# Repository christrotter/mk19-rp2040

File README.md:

# mk19-rp2040
Attempting to reduce soldering to a minimum - only need to solder the JST-XH headers.  This is the mainboard for the [ArcBoard-mk19](https://github.com/christrotter/qmk_firmware/tree/arcboard-series/keyboards/handwired/arcboard_mk19).

# Features
- On-board RP2040 w. 16MB flash (_based on splinktegrated and reference design_)
- USB-C connectivity for main, split, and screen indicators
- Boot and reset button headers
- Serial vbus power protection (_ESD, polyfuse, diode, etc_)
- External 5v input for LED power (_polyfuse, diode_)
- SPI shift registers to handle rows and cols - up to 256 keys per half - with row/col pin breakouts
- SPI LCD outputs via 0.5mm FPC connectors
- 0.3mm FPC connector for [Cyboard](https://www.cyboard.digital/product-page/dactyl-flex-pcbs) connectivity (or via [this](https://github.com/christrotter/mk19-flex-pcb))
- 0.5mm [macropad](https://github.com/christrotter/macropad-pcb) connector
- Dpad input with diodes (_[RKJXT w. encoder](https://github.com/christrotter/rkjxt-mini-breakout), [5-way](https://github.com/christrotter/5way-pcb), or [4-switch dpad](https://github.com/christrotter/microswitch-dpad)_)
- PMW33XX connector
- 2x [Ultrafalcon](https://github.com/christrotter/ultrafalcon) connectors
- VaniLED connector (_GND,5V,4 gpio; for controlling a secondary RP2040 that handles extra LEDs_)
- Audio, debug, spare pin, power breakouts
- Split-handedness pin solder jumper
- Optional SPI clock pull-down and SPI MISO pull-up resistors
- Test points

# Functional notes
- The LED DI/DO chain flows from main keys (_Cyboard_) to the macropad, then to the dpad (_bodged in post-production_), then UF1, UF2, keybar, screen indicators.
- ROW2COL
- Power LED only indicates you have 5v to the board
- Requires QMK's 'matrix lite' custom matrix feature
  - For more info regarding the custom matrix and shift register implementation, see here: https://github.com/christrotter/shift-register-spi-breakout-pcb
- With everything running it sits at around 1500 scan rate
- First flashing requires holding boot while plugging in main USB; subsequent flashes can use double-press reset button or `QK_BOOT`

# Production notes
- Due to putting the v-cuts on the edge cuts layer, all pcb renders are broken.  This is a known bug in JLC's process.  The pre-production verifications render correctly.
- Requires standard assembly which is a big price increase.
- Make sure to have 'production file verification' checked for PCB and PCBA.

## Post-production fixes
- USB lines were backwards
- Two pins (2 & 5) on the flash were reversed
- The v-cuts were on the wrong layer (should be on the edge cuts layer for JLC)

# PCB overview

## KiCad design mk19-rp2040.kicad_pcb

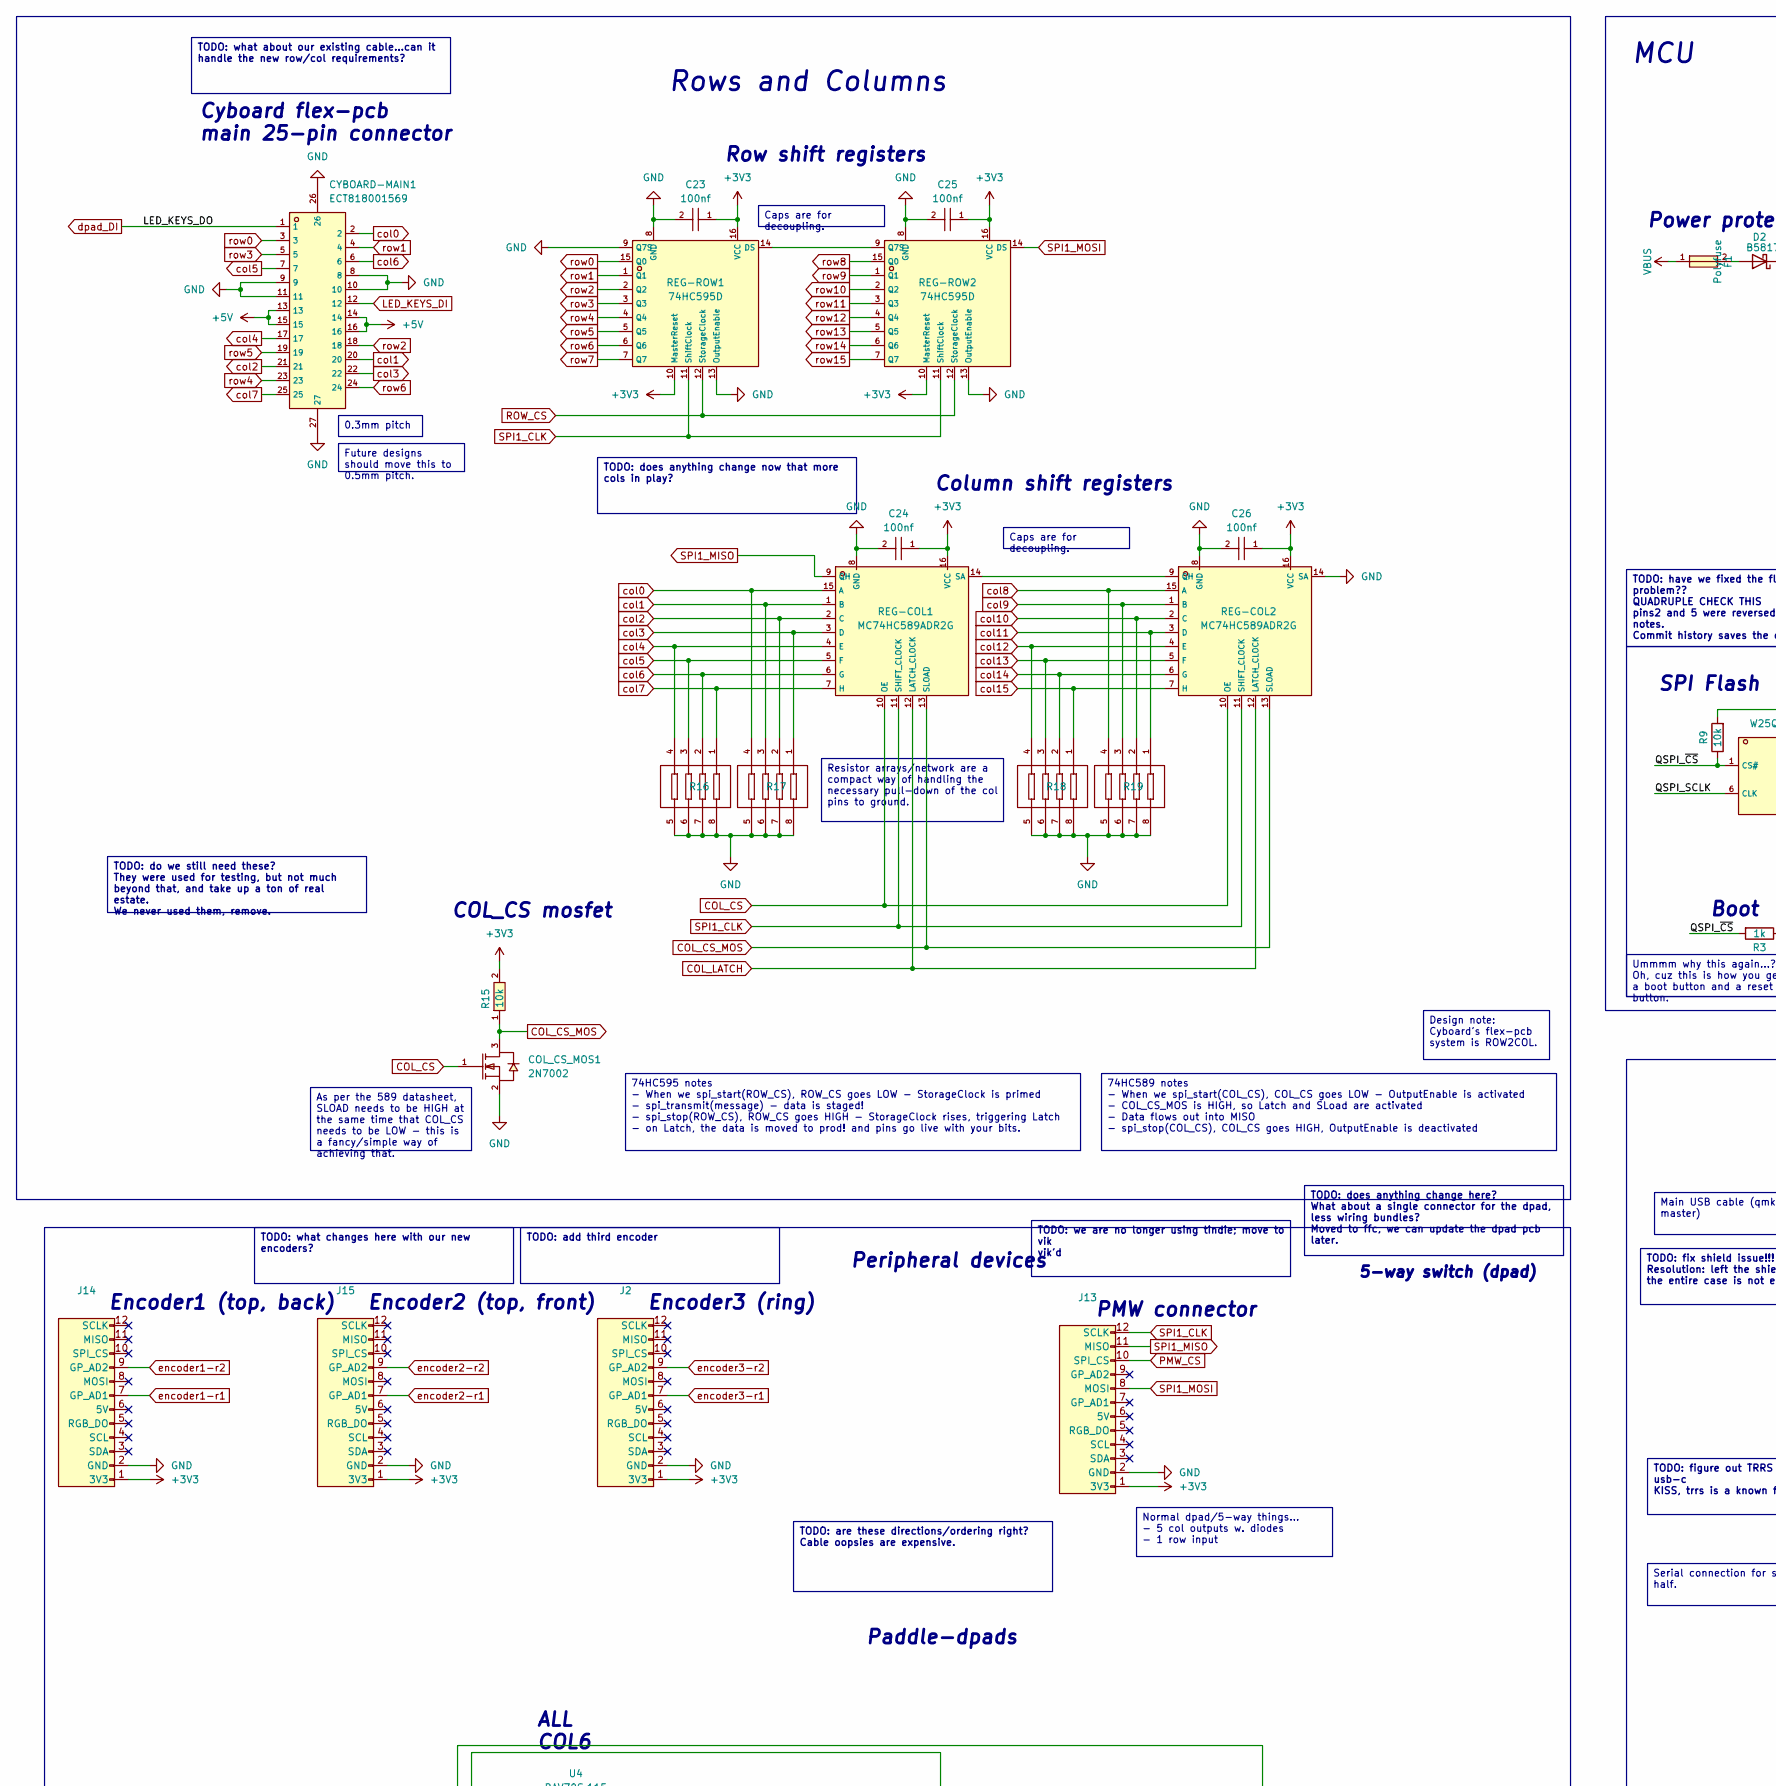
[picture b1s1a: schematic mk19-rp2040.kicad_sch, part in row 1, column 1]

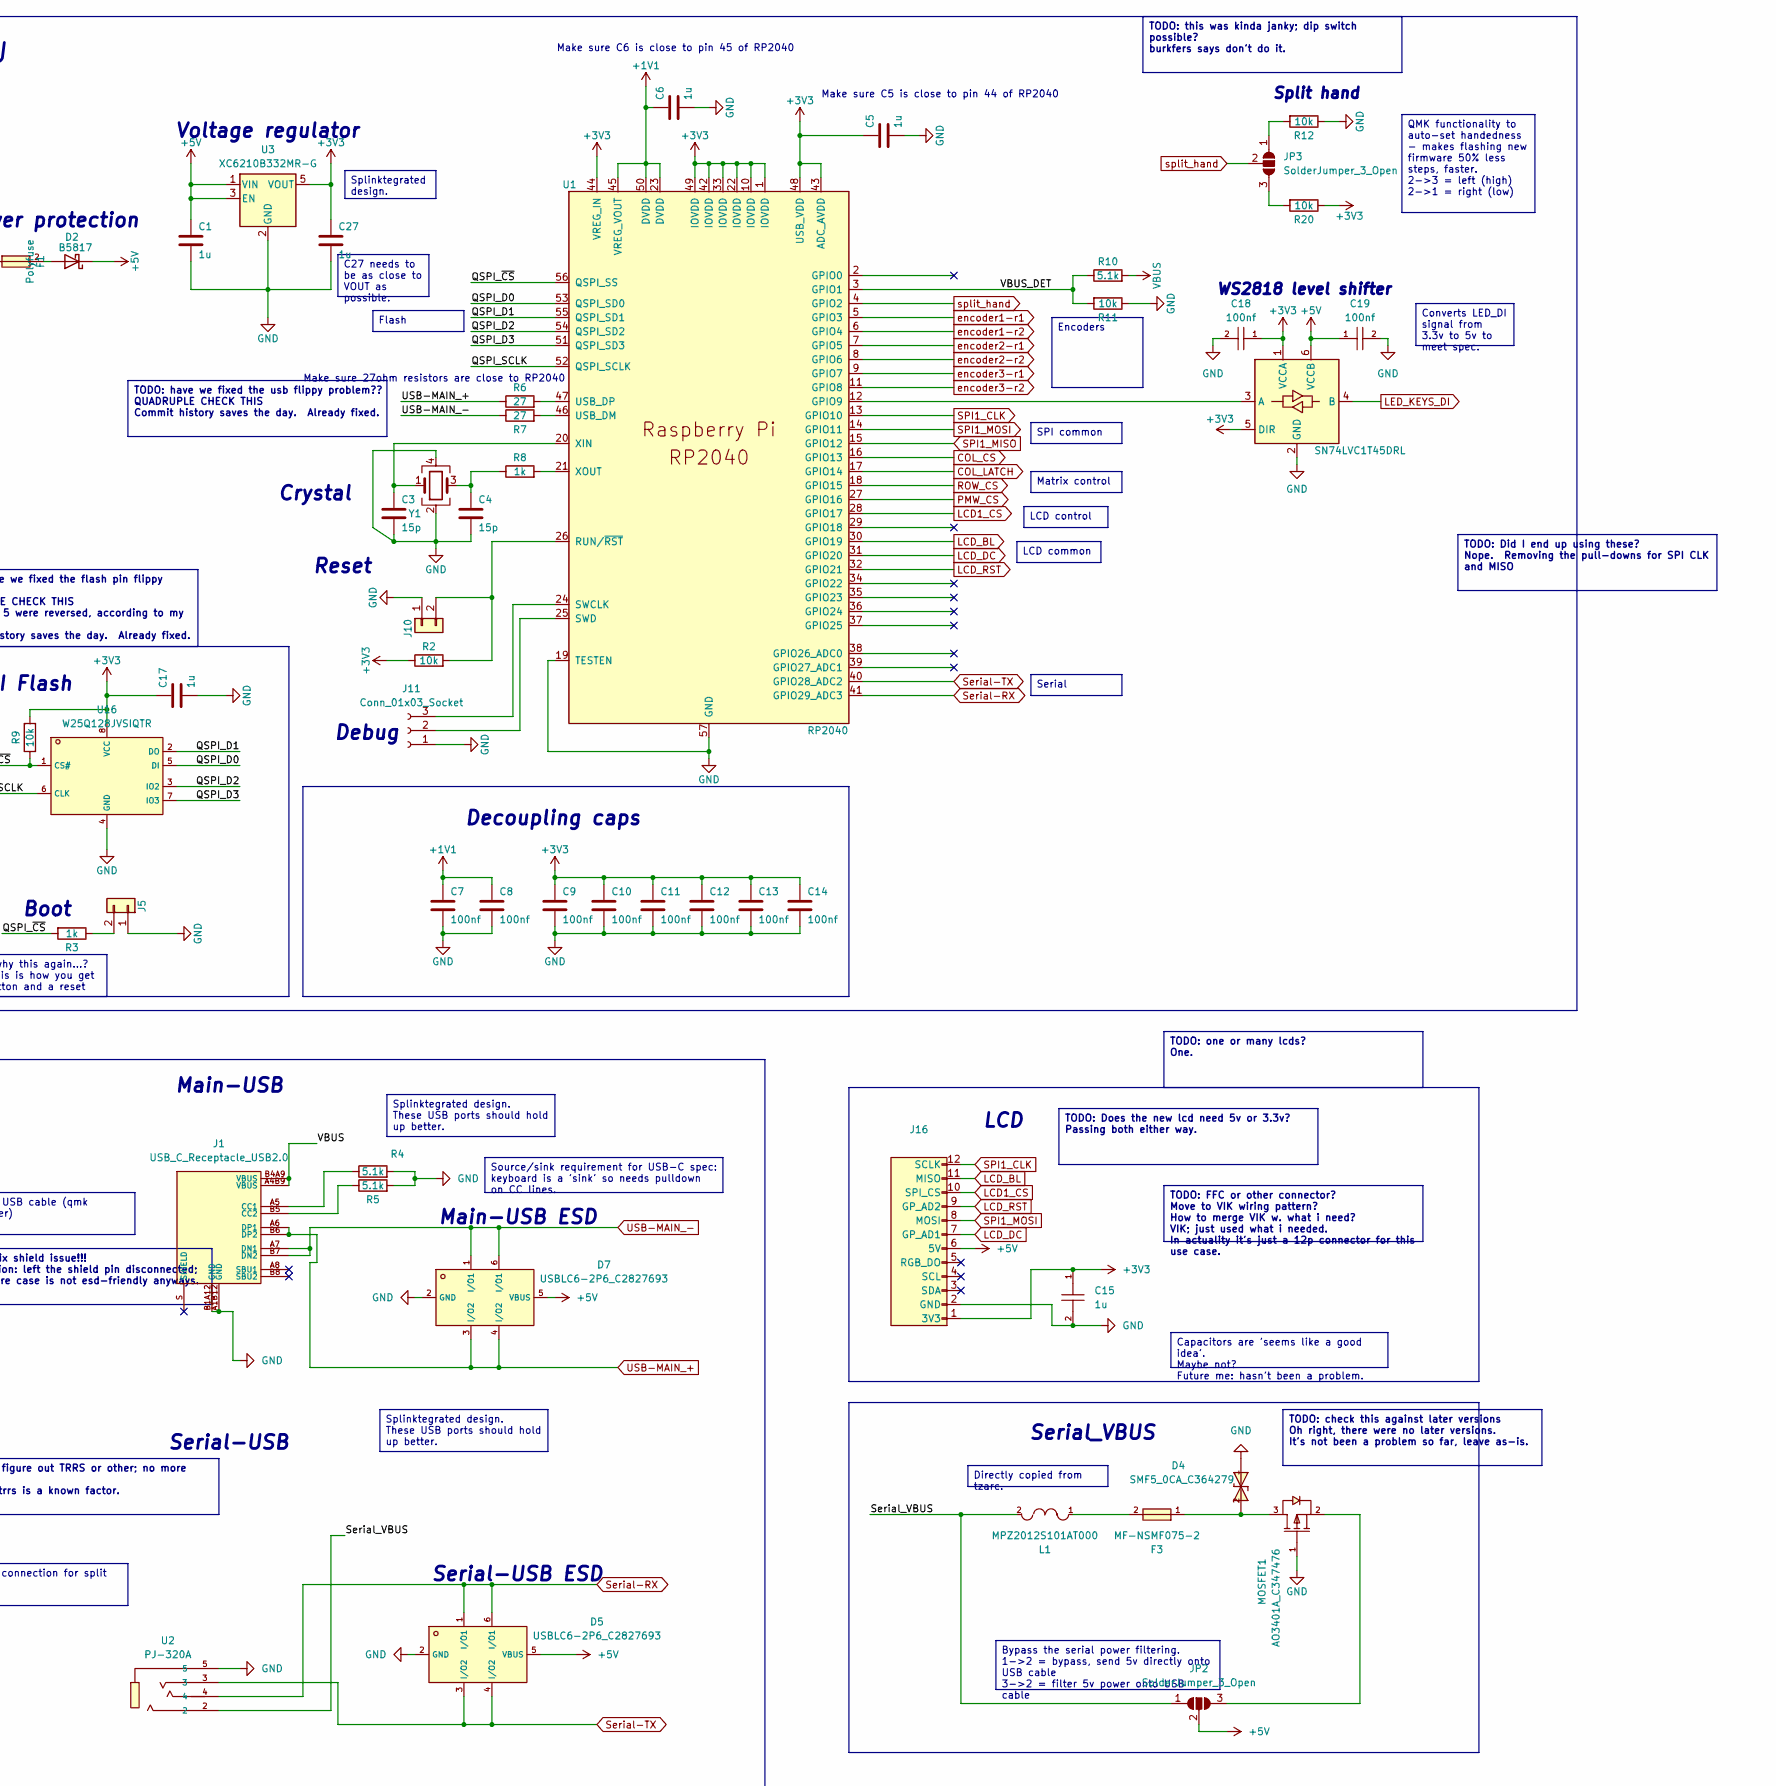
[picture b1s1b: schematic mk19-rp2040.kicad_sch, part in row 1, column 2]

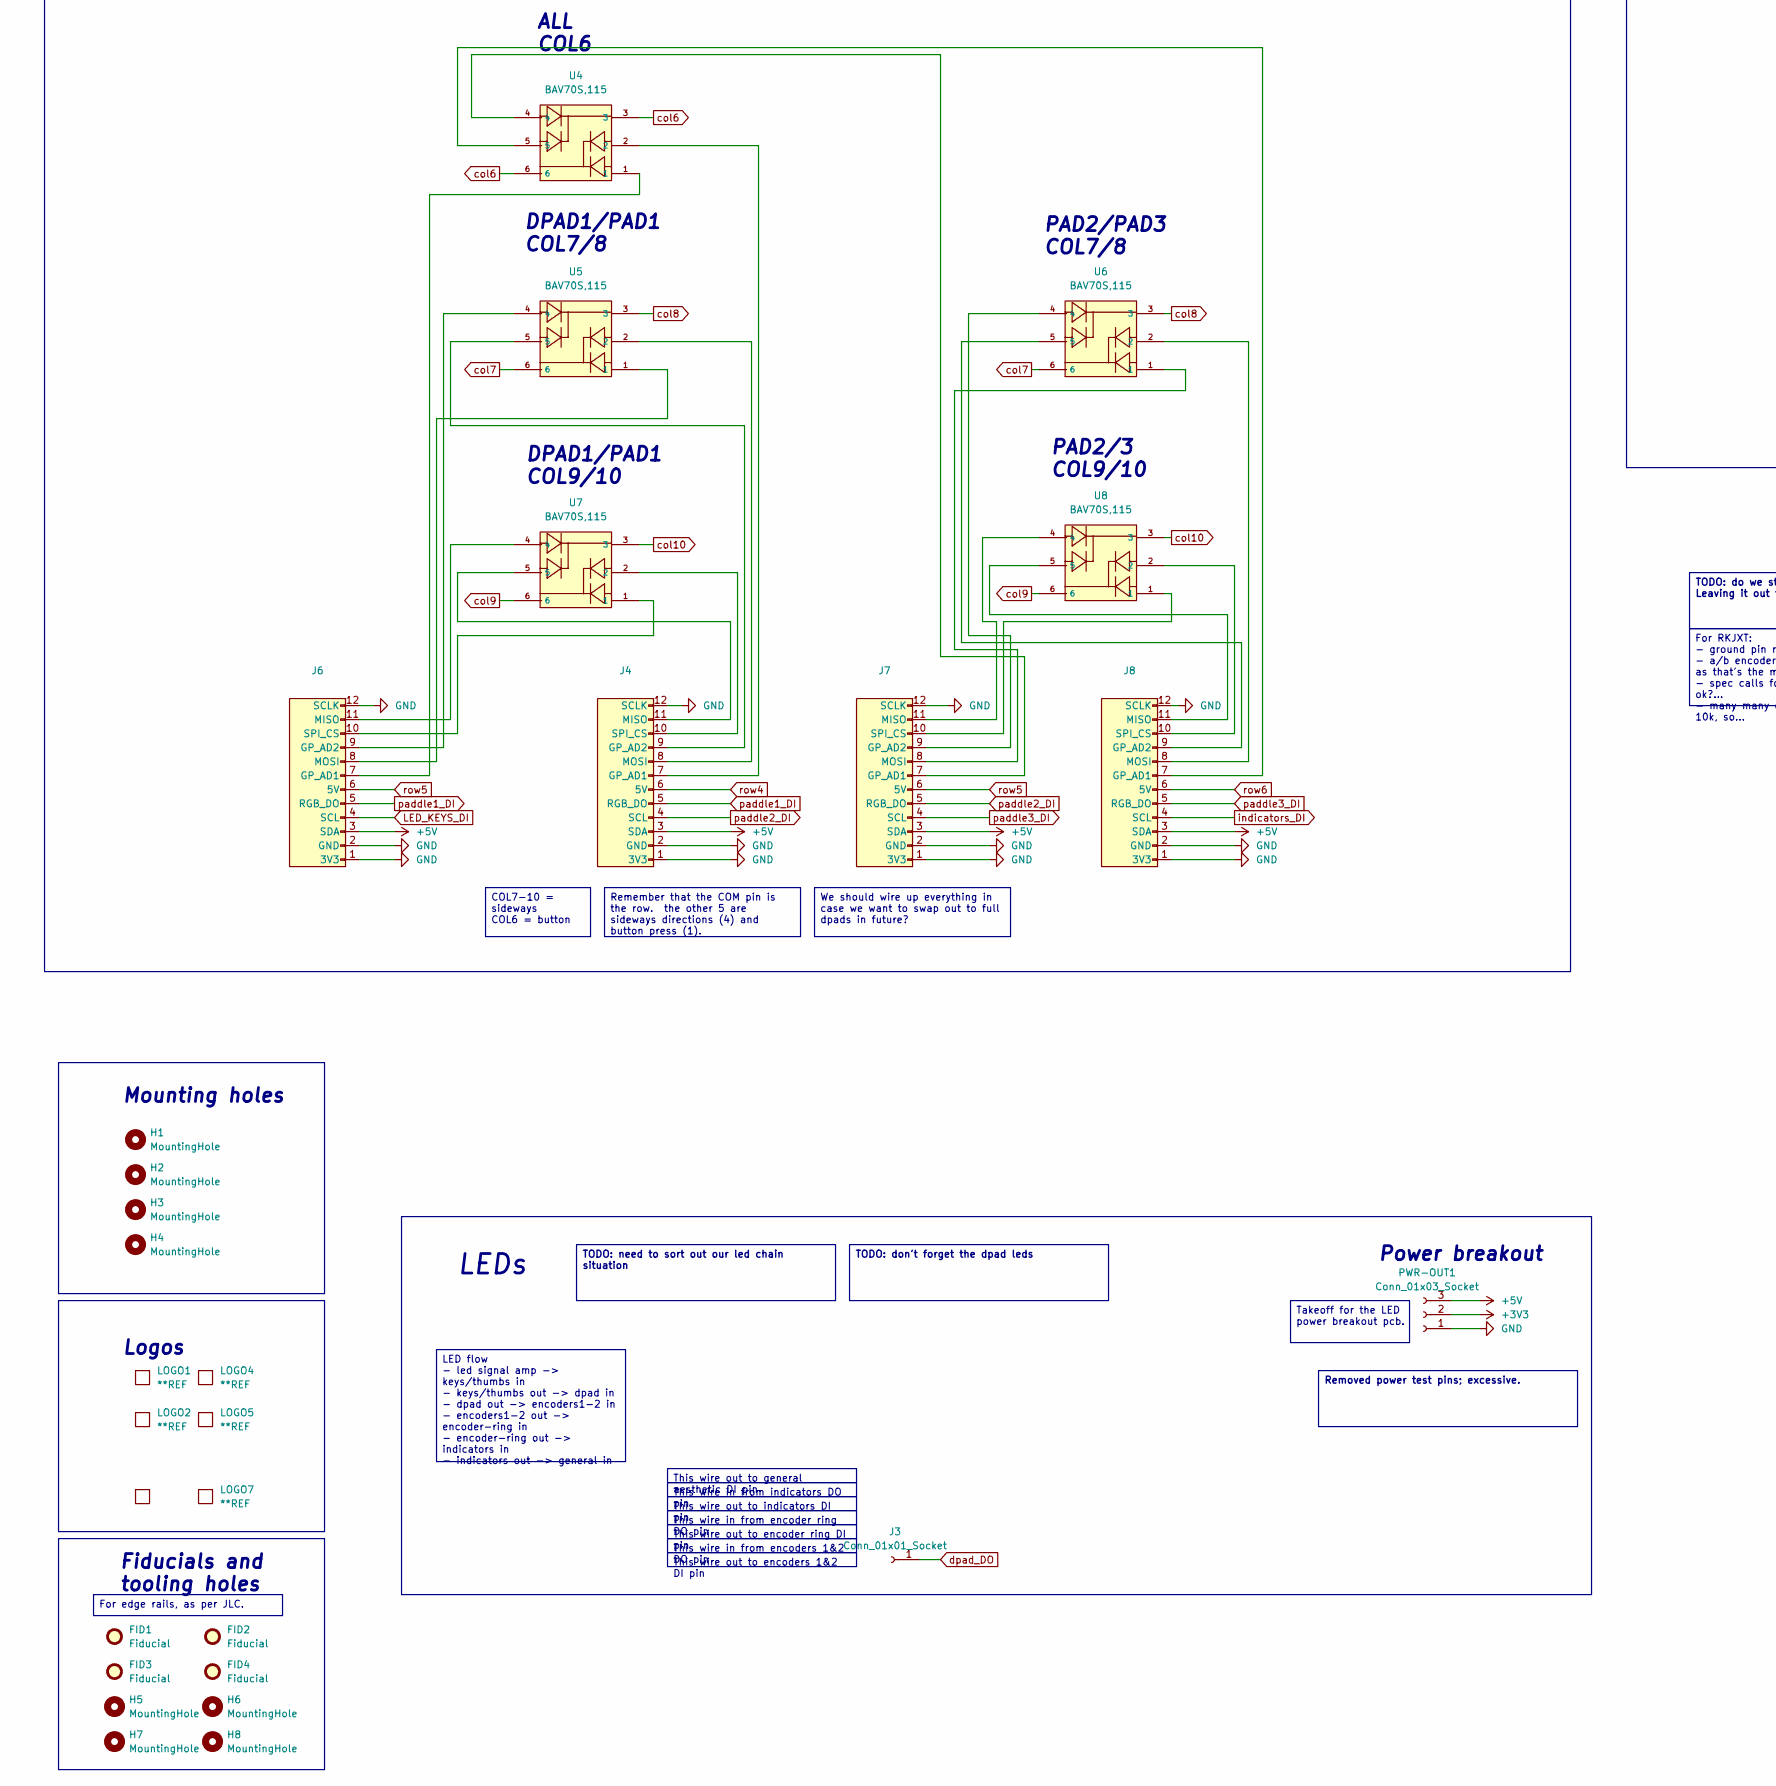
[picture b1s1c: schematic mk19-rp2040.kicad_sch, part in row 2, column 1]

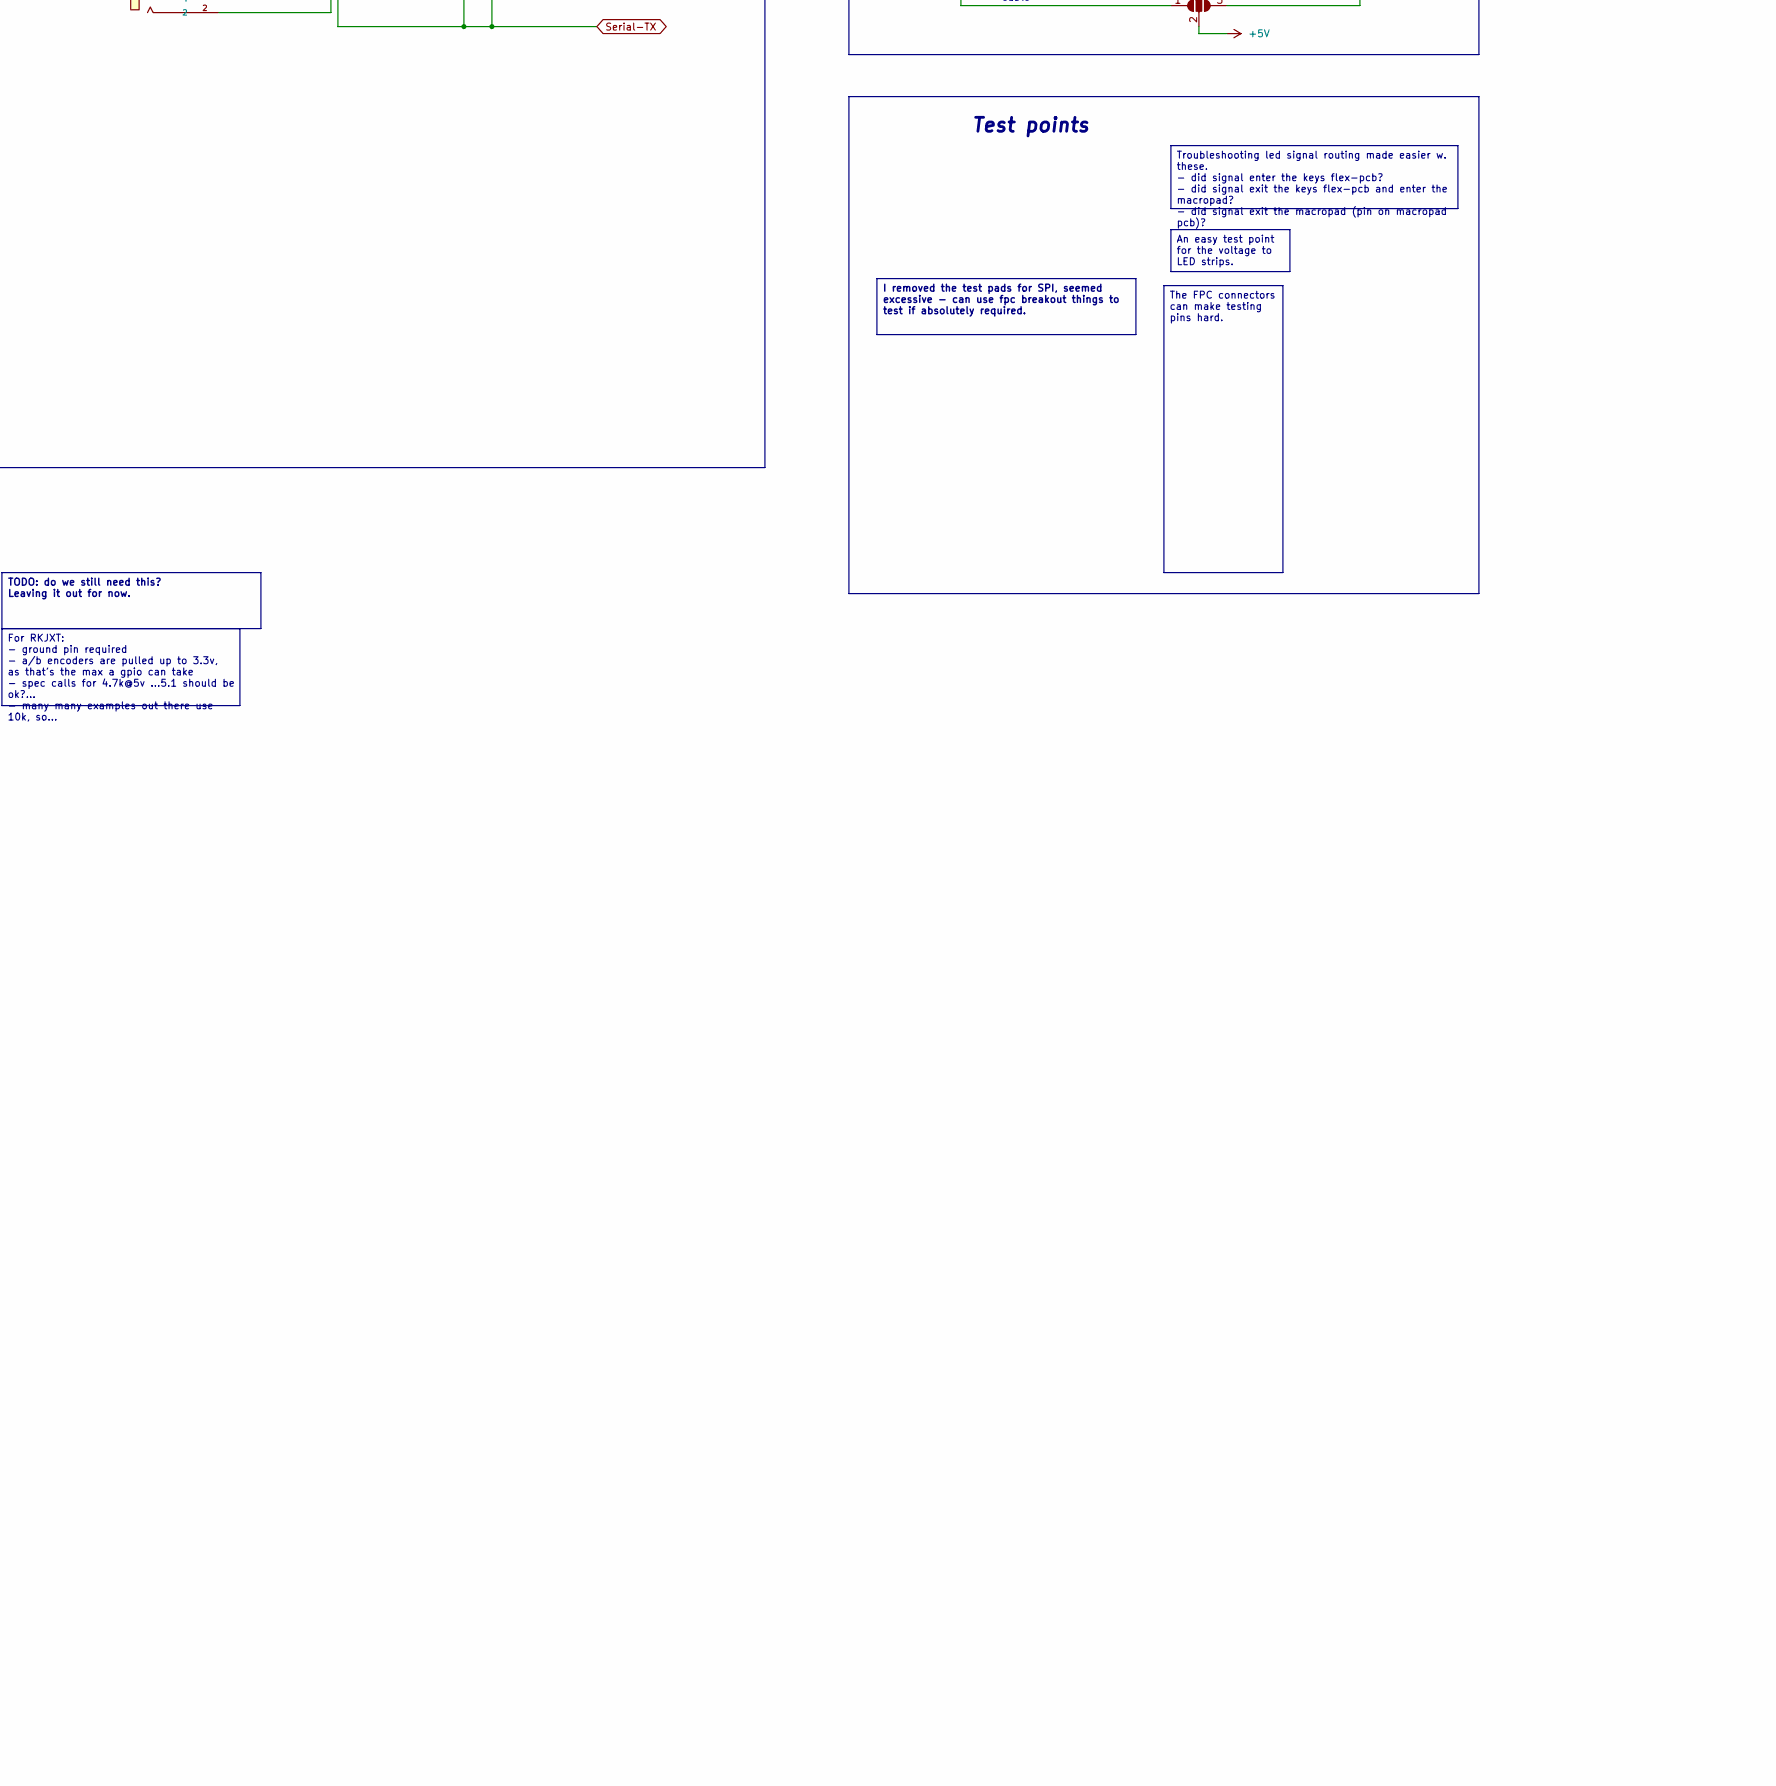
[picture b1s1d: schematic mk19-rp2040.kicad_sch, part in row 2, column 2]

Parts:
C1, C5, C6, C15, C17, C27: 1u; C0402; LCSC C52923
C3, C4: 15p; C0402; LCSC C1548
C7, C8, C9, C10, C11, C12, C13, C14, C18, C19, C23, C24, C25, C26: 100nf; C0402; LCSC C1525
COL_CS_MOS1: 2N7002; SOT-23-3_L2.9-W1.3-P1.90-LS2.4-BR; LCSC C8545
CYBOARD-MAIN1: ECT818001569; FPC-SMD_ECT818001569; LCSC C711420
D2: B5817; D_SOD-323; LCSC C123899
D4: SMF5_0CA_C364279; SOD-123FL_L2.8-W1.8-LS3.7-BI; LCSC C364279
D5, D7: USBLC6-2P6_C2827693; SOT-666-6_L1.6-W1.2-P0.50-LS1.6-BL; LCSC C2827693
F1: Polyfuse; F1206; LCSC C2892425
F3: MF-NSMF075-2; F1206; LCSC C89653
FID1, FID2, FID3, FID4: Fiducial; Fiducial_1mm_Mask3mm
H1, H2, H3, H4: MountingHole; MountingHole_3.2mm_M3_Pad_Via
H5, H6, H7, H8: MountingHole; hole-tooling-2mm
J1: USB_C_Receptacle_USB2.0; USB-C-SMD_12P-P0.50-H-F_TYPE-C-31-M-14; LCSC C223907
J2, J4, J6, J7, J8, J13, J14, J15, J16: FFC-SMD_FFC05001-12SBA124W5M
J3: Conn_01x01_Socket; PinHeader_1x01_P2.54mm_Vertical
J5, J10: Conn_01x02; PinSocket_1x02_P2.54mm_Vertical
J11: Conn_01x03_Socket; PinHeader_1x03_P2.54mm_Vertical
JP2, JP3: SolderJumper_3_Open; SolderJumper-3_P1.3mm_Open_Pad1.0x1.5mm
L1: MPZ2012S101AT000; L0805; LCSC C15957
LED-LVL1: SN74LVC1T45DRL; SOT-563_L1.6-W1.2-P0.50-LS1.6-BR; MPN SN74LVC1T45DRLR; JLC Basic N
LOGO1, LOGO4: **REF; awesome-logo
LOGO2, LOGO5: **REF; qmk-lite
LOGO7: **REF; cyboard-logo-10mm
LOGO8: **REF; qr-mk19-rp2040-10mm
MOSFET1: AO3401A_C347476; SOT-23_L2.9-W1.3-P1.90-LS2.4-BR; LCSC C15127
PWR-OUT1: Conn_01x03_Socket; PinHeader_1x03_P2.54mm_Vertical
R2, R9, R11, R12, R15, R20: 10k; R0402; LCSC C25744
R3, R8: 1k; R0402; LCSC C11702
R4, R5, R10: 5.1k; R0402; LCSC C25905
R6, R7: 27; R0402; LCSC C25100
R16, R17, R18, R19: 4D03WGJ0103T5E; RES-ARRAY-SMD_0603-8P-L3.2-W1.6-BL; LCSC C29718
REG-COL1, REG-COL2: MC74HC589ADR2G; SOIC-16_L9.9-W3.9-P1.27-LS6.0-BL; LCSC C7343
REG-ROW1, REG-ROW2: 74HC595D; SOIC-16_L9.9-W3.9-P1.27-LS6.0-BL; LCSC C5947
U1: RP2040; LQFN-56_L7.0-W7.0-P0.4-EP; LCSC C2040
U2: PJ-320A; AUDIO-TH_XKB_PJ-320A; LCSC C2884926
U3: XC6210B332MR-G; SOT-23-5; LCSC C82942
U4, U5, U6, U7, U8: BAV70S,115; SOT-363-6_L2.0-W1.3-P0.65-LS2.1-BL; LCSC C455031
U16: W25Q128JVSIQTR; SOIC-8_L5.3-W5.3-P1.27-LS8.0-BL; LCSC C97521
Y1: Crystal_GND24; Crystal_SMD_2520-4Pin_2.5x2.0mm; LCSC C2149204

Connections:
+1V1: C6.1, C7.1, C8.1, U1.23 (DVDD), U1.45 (VREG_VOUT), U1.50 (DVDD)
+3V3: C5.1, C9.1, C10.1, C11.1, C12.1, C13.1, C14.1, C15.1, C17.1, C18.1, C23.1, C24.1, C25.1, C26.1, C27.1, J2.1 (3V3), J13.1 (3V3), J14.1 (3V3), J15.1 (3V3), J16.1 (3V3), LED-LVL1.1 (VCCA), LED-LVL1.5 (DIR), PWR-OUT1.2, R2.1, R9.2, R15.2, R20.1, REG-COL1.16 (VCC), REG-COL2.16 (VCC), REG-ROW1.10 (MasterReset), REG-ROW1.16 (VCC), REG-ROW2.10 (MasterReset), REG-ROW2.16 (VCC), U1.1 (IOVDD), U1.10 (IOVDD), U1.22 (IOVDD), U1.33 (IOVDD), U1.42 (IOVDD), U1.43 (ADC_AVDD), U1.44 (VREG_IN), U1.48 (USB_VDD), U1.49 (IOVDD), U3.5 (VOUT), U16.8 (VCC)
+5V: C1.1, C19.1, CYBOARD-MAIN1.13, CYBOARD-MAIN1.14, CYBOARD-MAIN1.15, CYBOARD-MAIN1.16, D2.1 (K), D5.5 (VBUS), D7.5 (VBUS), J4.3 (SDA), J6.3 (SDA), J7.3 (SDA), J8.3 (SDA), J16.6 (5V), JP2.2 (C), LED-LVL1.6 (VCCB), PWR-OUT1.3, U3.1 (VIN), U3.3 (EN)
/QSPI_D0: U1.53 (QSPI_SD0), U16.5 (DI)
/QSPI_D1: U1.55 (QSPI_SD1), U16.2 (DO)
/QSPI_D2: U1.54 (QSPI_SD2), U16.3 (IO2)
/QSPI_D3: U1.51 (QSPI_SD3), U16.7 (IO3)
/QSPI_SCLK: U1.52 (QSPI_SCLK), U16.6 (CLK)
/QSPI_~CS: R3.2, R9.1, U1.56 (QSPI_SS), U16.1 (CS#)
/Serial_VBUS: JP2.1 (A), L1.2, U2.2
/VBUS_DET: R10.1, R11.2, U1.3 (GPIO1)
COL_CS: COL_CS_MOS1.1 (G), REG-COL1.10 (OE), REG-COL2.10 (OE), U1.16 (GPIO13)
COL_CS_MOS: COL_CS_MOS1.3 (D), R15.1, REG-COL1.13 (SLOAD), REG-COL2.13 (SLOAD)
COL_LATCH: REG-COL1.12 (LATCH_CLOCK), REG-COL2.12 (LATCH_CLOCK), U1.17 (GPIO14)
GND: C1.2, C3.2, C4.2, C5.2, C6.2, C7.2, C8.2, C9.2, C10.2, C11.2, C12.2, C13.2, C14.2, C15.2, C17.2, C18.2, C19.2, C23.2, C24.2, C25.2, C26.2, C27.2, COL_CS_MOS1.2 (S), CYBOARD-MAIN1.8, CYBOARD-MAIN1.9, CYBOARD-MAIN1.10, CYBOARD-MAIN1.11, CYBOARD-MAIN1.26, CYBOARD-MAIN1.27, D4.1 (K), D5.2 (GND), D7.2 (GND), J1.A1B12 (GND), J1.B1A12 (GND), J2.2 (GND), J4.1 (3V3), J4.2 (GND), J4.12 (SCLK), J5.1, J6.1 (3V3), J6.2 (GND), J6.12 (SCLK), J7.1 (3V3), J7.2 (GND), J7.12 (SCLK), J8.1 (3V3), J8.2 (GND), J8.12 (SCLK), J10.1, J11.1, J13.2 (GND), J14.2 (GND), J15.2 (GND), J16.2 (GND), LED-LVL1.2 (GND), MOSFET1.1 (G), PWR-OUT1.1, R4.2, R5.2, R11.1, R12.1, R16.5, R16.6, R16.7, R16.8, R17.5, R17.6, R17.7, R17.8, R18.5, R18.6, R18.7, R18.8, R19.5, R19.6, R19.7, R19.8, REG-COL1.8 (GND), REG-COL2.8 (GND), REG-COL2.14 (SA), REG-ROW1.8 (GND), REG-ROW1.9 (Q7S), REG-ROW1.13 (OutputEnable), REG-ROW2.8 (GND), REG-ROW2.13 (OutputEnable), U1.19 (TESTEN), U1.57 (GND), U2.5, U3.2 (GND), U16.4 (GND), Y1.2, Y1.4
LCD1_CS: J16.10 (SPI_CS), U1.28 (GPIO17)
LCD_BL: J16.11 (MISO), U1.30 (GPIO19)
LCD_DC: J16.7 (GP_AD1), U1.31 (GPIO20)
LCD_RST: J16.9 (GP_AD2), U1.32 (GPIO21)
LED_KEYS_DI: CYBOARD-MAIN1.12, J6.4 (SCL), LED-LVL1.4 (B)
unnamed: C4.1, R8.1, Y1.3
unnamed: D2.2 (A), F1.2
unnamed: D4.2 (A), F3.1, MOSFET1.3 (D)
unnamed: F3.2, L1.1
unnamed: J1.A5 (CC1), R4.1
unnamed: J1.B5 (CC2), R5.1
unnamed: J4.7 (GP_AD1), U4.2
unnamed: J4.9 (GP_AD2), U5.5
unnamed: J4.11 (MISO), U7.5
unnamed: J4.8 (MOSI), U5.2
unnamed: J4.10 (SPI_CS), U7.2
unnamed: J5.2, R3.1
unnamed: J6.7 (GP_AD1), U4.1
unnamed: J6.9 (GP_AD2), U5.4
unnamed: J6.11 (MISO), U7.4
unnamed: J6.8 (MOSI), U5.1
unnamed: J6.10 (SPI_CS), U7.1
unnamed: J7.7 (GP_AD1), U4.4
unnamed: J7.9 (GP_AD2), U6.4
unnamed: J7.11 (MISO), U8.4
unnamed: J7.8 (MOSI), U6.1
unnamed: J7.10 (SPI_CS), U8.1
unnamed: J8.7 (GP_AD1), U4.5
unnamed: J8.9 (GP_AD2), U6.5
unnamed: J8.11 (MISO), U8.5
unnamed: J8.8 (MOSI), U6.2
unnamed: J8.10 (SPI_CS), U8.2
unnamed: J10.2, R2.2, U1.26 (RUN/~RST)
unnamed: J11.2, U1.25 (SWD)
unnamed: J11.3, U1.24 (SWCLK)
unnamed: JP2.3 (B), MOSFET1.2 (S)
unnamed: JP3.1 (A), R12.2
unnamed: JP3.3 (B), R20.2
unnamed: LED-LVL1.3 (A), U1.12 (GPIO9)
unnamed: REG-COL1.14 (SA), REG-COL2.9 (QH)
unnamed: REG-ROW1.14 (DS), REG-ROW2.9 (Q7S)
unnamed: R7.2, U1.46 (USB_DM)
unnamed: R6.2, U1.47 (USB_DP)
unnamed: C3.1, U1.20 (XIN), Y1.1
unnamed: R8.2, U1.21 (XOUT)
PMW_CS: J13.10 (SPI_CS), U1.27 (GPIO16)
ROW_CS: REG-ROW1.12 (StorageClock), REG-ROW2.12 (StorageClock), U1.18 (GPIO15)
SPI1_CLK: J13.12 (SCLK), J16.12 (SCLK), REG-COL1.11 (SHIFT_CLOCK), REG-COL2.11 (SHIFT_CLOCK), REG-ROW1.11 (ShiftClock), REG-ROW2.11 (ShiftClock), U1.13 (GPIO10)
SPI1_MISO: J13.11 (MISO), REG-COL1.9 (QH), U1.15 (GPIO12)
SPI1_MOSI: J13.8 (MOSI), J16.8 (MOSI), REG-ROW2.14 (DS), U1.14 (GPIO11)
Serial-RX: D5.1 (I/O1), D5.6 (I/O1), U1.41 (GPIO29_ADC3), U2.4
Serial-TX: D5.3 (I/O2), D5.4 (I/O2), U1.40 (GPIO28_ADC2), U2.3
USB-MAIN_+: D7.3 (I/O2), D7.4 (I/O2), J1.A6 (DP1), J1.B6 (DP2), R6.1
USB-MAIN_-: D7.1 (I/O1), D7.6 (I/O1), J1.A7 (DN1), J1.B7 (DN2), R7.1
VBUS: F1.1, J1.A4B9 (VBUS), J1.B4A9 (VBUS), R10.2
col0: CYBOARD-MAIN1.2, R17.4, REG-COL1.15 (A)
col1: CYBOARD-MAIN1.20, R17.3, REG-COL1.1 (B)
col2: CYBOARD-MAIN1.21, R17.2, REG-COL1.2 (C)
col3: CYBOARD-MAIN1.22, R17.1, REG-COL1.3 (D)
col4: CYBOARD-MAIN1.17, R16.4, REG-COL1.4 (E)
col5: CYBOARD-MAIN1.7, R16.3, REG-COL1.5 (F)
col6: CYBOARD-MAIN1.6, R16.2, REG-COL1.6 (G), U4.3, U4.6
col7: CYBOARD-MAIN1.25, R16.1, REG-COL1.7 (H), U5.6, U6.6
col8: R19.4, REG-COL2.15 (A), U5.3, U6.3
col9: R19.3, REG-COL2.1 (B), U7.6, U8.6
col10: R19.2, REG-COL2.2 (C), U7.3, U8.3
col11: R19.1, REG-COL2.3 (D)
col12: R18.4, REG-COL2.4 (E)
col13: R18.3, REG-COL2.5 (F)
col14: R18.2, REG-COL2.6 (G)
col15: R18.1, REG-COL2.7 (H)
dpad_DI: CYBOARD-MAIN1.1
dpad_DO: J3.1
encoder1-r1: J14.7 (GP_AD1), U1.5 (GPIO3)
encoder1-r2: J14.9 (GP_AD2), U1.6 (GPIO4)
encoder2-r1: J15.7 (GP_AD1), U1.7 (GPIO5)
encoder2-r2: J15.9 (GP_AD2), U1.8 (GPIO6)
encoder3-r1: J2.7 (GP_AD1), U1.9 (GPIO7)
encoder3-r2: J2.9 (GP_AD2), U1.11 (GPIO8)
indicators_DI: J8.4 (SCL)
paddle1_DI: J4.5 (RGB_DO), J6.5 (RGB_DO)
paddle2_DI: J4.4 (SCL), J7.5 (RGB_DO)
paddle3_DI: J7.4 (SCL), J8.5 (RGB_DO)
row0: CYBOARD-MAIN1.3, REG-ROW1.15 (Q0)
row1: CYBOARD-MAIN1.4, REG-ROW1.1 (Q1)
row2: CYBOARD-MAIN1.18, REG-ROW1.2 (Q2)
row3: CYBOARD-MAIN1.5, REG-ROW1.3 (Q3)
row4: CYBOARD-MAIN1.23, J4.6 (5V), REG-ROW1.4 (Q4)
row5: CYBOARD-MAIN1.19, J6.6 (5V), J7.6 (5V), REG-ROW1.5 (Q5)
row6: CYBOARD-MAIN1.24, J8.6 (5V), REG-ROW1.6 (Q6)
row7: REG-ROW1.7 (Q7)
row8: REG-ROW2.15 (Q0)
row9: REG-ROW2.1 (Q1)
row10: REG-ROW2.2 (Q2)
row11: REG-ROW2.3 (Q3)
row12: REG-ROW2.4 (Q4)
row13: REG-ROW2.5 (Q5)
row14: REG-ROW2.6 (Q6)
row15: REG-ROW2.7 (Q7)
split_hand: JP3.2 (C), U1.4 (GPIO2)

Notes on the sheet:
Rows and Columns
Main-USB
SPI Flash
Serial_VBUS
LEDs
Test points
WS2818 level shifter
Make sure C5 is close to pin 44 of RP2040
DPAD1/PAD1 COL7/8
Voltage regulator
Power breakout
Cyboard flex-pcb main 25-pin connector
LCD
PAD2/PAD3 COL7/8
Make sure C6 is close to pin 45 of RP2040
Boot
Decoupling caps
Mounting holes
Peripheral devices
Main-USB ESD
Row shift registers
Serial-USB ESD
Crystal
Reset
DPAD1/PAD1 COL9/10
Fiducials and tooling holes
Encoder2 (top, front)
Encoder1 (top, back)
Serial-USB
MCU
Paddle-dpads
PAD2/3 COL9/10
5-way switch (dpad)
PMW connector
Split hand
Make sure 27ohm resistors are close to RP2040
Power protection
Logos
ALL COL6
Column shift registers

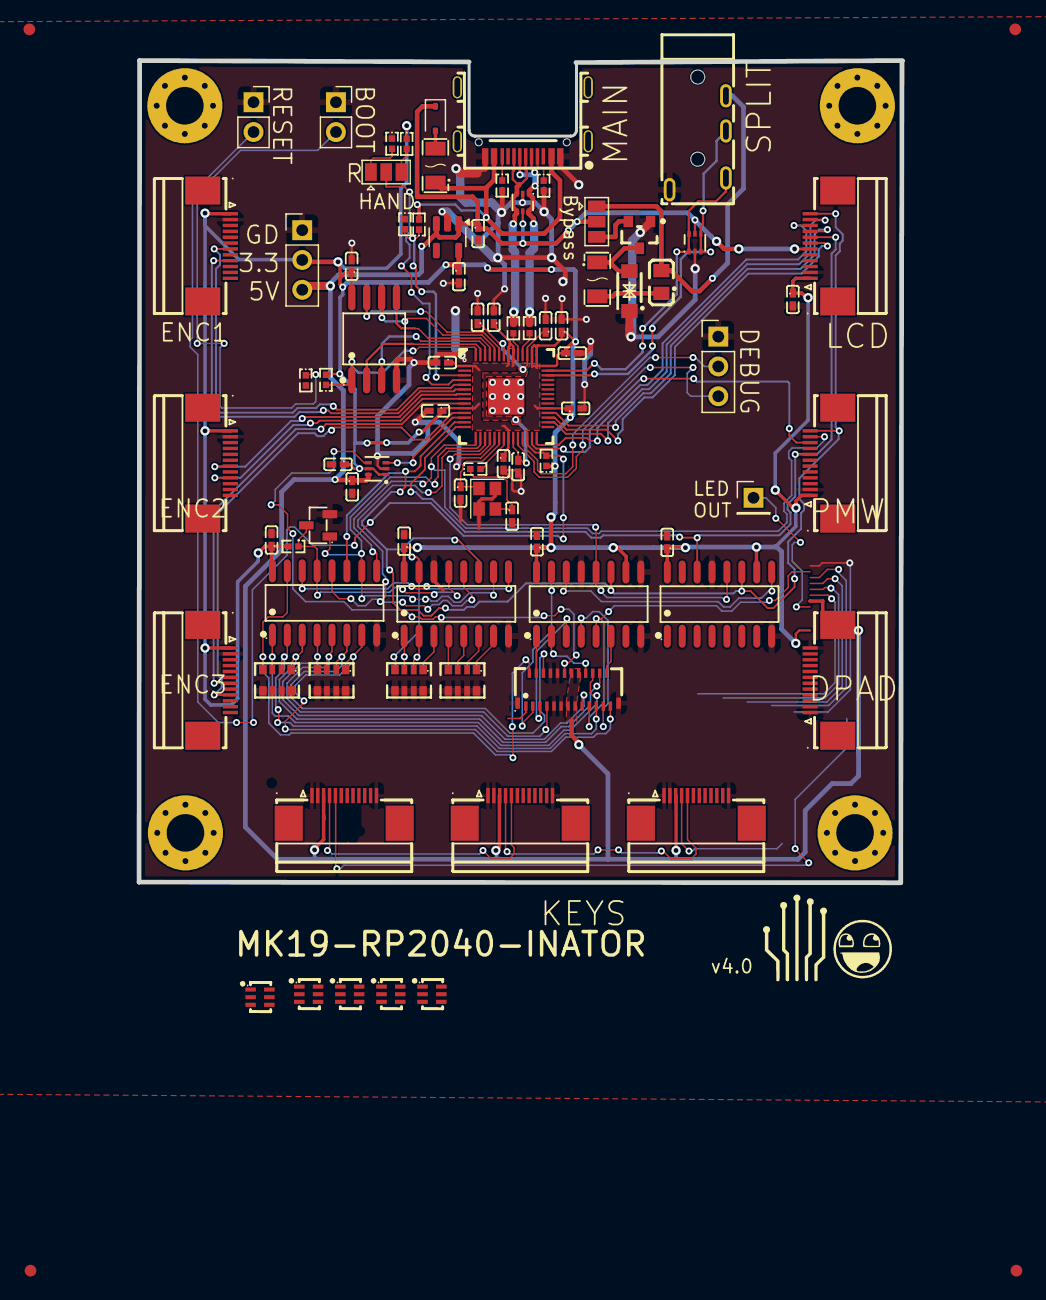
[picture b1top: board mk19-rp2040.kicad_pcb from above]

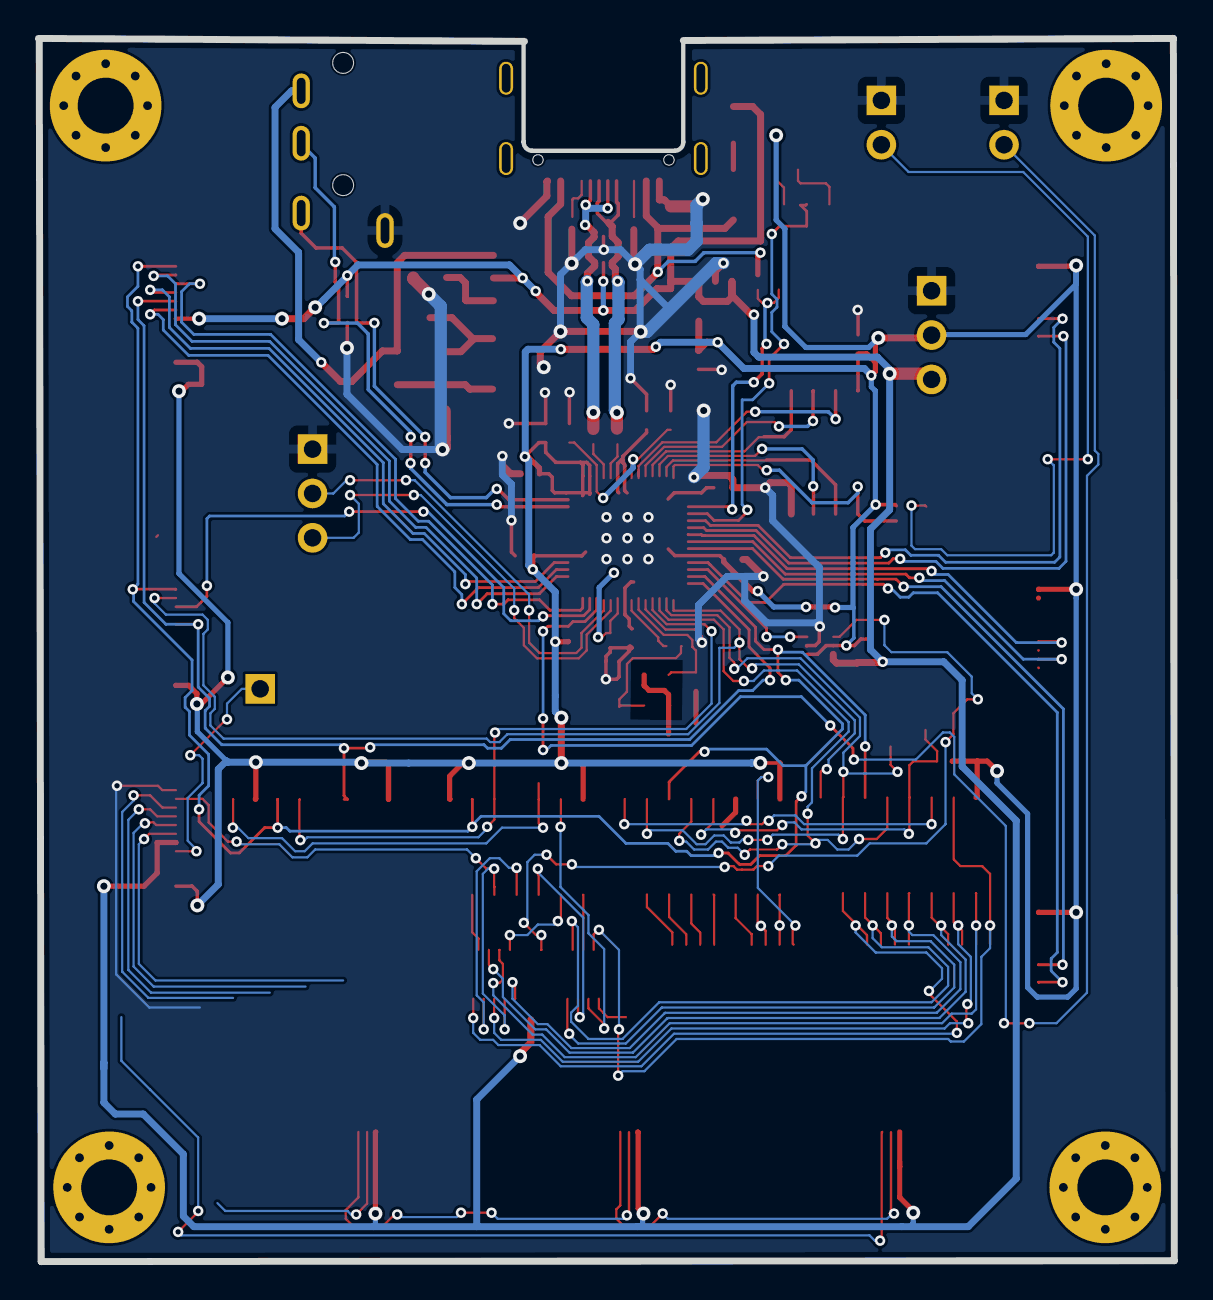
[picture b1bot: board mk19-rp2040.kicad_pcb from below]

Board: 2 copper layers, 65.1 x 70.0 mm, 98 parts (3 on the bottom side), 103 nets.

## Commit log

2024-03-12 starting work, base schematic created
2024-03-13 starting on first pass at placing components
2024-03-19 added handedness, led signal breakout, more
2024-03-19 fixed led situation, added diodes, fixed eh-xh confusion, more
2024-03-20 more fixes, including rkjxt
2024-03-20 adding a lot of notes, fixes
2024-03-20 minor formatting
2024-03-20 some bad footprints, other fixes
2024-03-20 progress update
2024-03-21 fixes
2024-03-21 getting close to having the rp2040 traced
2024-03-22 more progress
2024-03-22 even more progress, starting to come together.
2024-03-23 almost done
2024-03-23 drc passing, everything hooked up
2024-03-23 more changes, pcba insights coming next
2024-03-24 reworking some of this, copy paste introduced errors whee
2024-03-25 drc passing, bom generating correctly, silkscreen v1
2024-03-25 getting manufacturing bits ready
2024-03-25 moving away from through-hole test points
2024-03-25 relocating boot debug reset to edges of board, edge rail improvements
2024-03-27 just about ready to produce
2024-03-27 minor fix
2024-03-27 reworking the voltage regulator capacitors
2024-03-27 removing the other 10u caps and relocating the power in plug
2024-03-27 replaced the macro connector with a more solid-looking part, more rework
2024-03-28 updating silkscreens
2024-03-29 fixing silkscreen, changing out polyfuses to larger, improving trace routing
2024-03-29 adding the pull up-down for spi miso and sck, with solder jumpers
2024-04-03 moving things around for better physical fitment
2024-04-04 shipped to jlc
2024-04-27 adding images
2024-04-27 fixing the manufacturing bugs - usb data crossed, flash pins 2 and 5 reversed, and v-cuts on wrong layer
2024-04-28 how could i forget the inator
2024-05-05 fixing layer on mounting hole footprint
2024-05-05 adding lck files to gitignore
2024-05-05 removing the serial power bypass
2024-05-05 wups
2024-05-05 moving reset
2025-07-18 starting rev4 pruning and converting
2025-07-19 savegame, saturday
2025-07-21 before investigating stm32
